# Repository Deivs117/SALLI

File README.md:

# SALLI: Salamander Autonomous Locomotion on Land Infrastructure

SALLI is an open-source, low-cost, and modular mechatronic platform designed to study bio-inspired terrestrial locomotion. Drawing inspiration from the sprawling gait of the salamander, this project integrates custom 3D-printed mechanical linkages, dedicated modular printed circuit boards (PCBs), lightweight embedded ESP-IDF firmware, and high-level Python control algorithms.

---

## Project Vision & Philosophy

Traditional robotics platforms often suffer from high manufacturing costs, complex monolithic assemblies, and poor reparability. SALLI was conceived under a different paradigm:
* **True Modularity:** Every physical segment—whether a spinal oscillator, a locomotor leg, or a sensory head—uses a standardized mechanical and electrical connection interface. Segments can be chain-linked dynamically to increase or decrease the robot's degrees of freedom (DoF).
* **Low Cost & Accessibility:** Designed to be accessible to students, researchers, and hobbyists. The structural parts are optimized for standard FDM 3D printing, and the electronics rely on budget-friendly, high-performance ESP32-C3 microcontrollers and standard micro servos.
* **Easy Maintenance & Repair:** Field repairs can be executed swiftly. Damage to a single segment does not compromise the whole robot; the offending module can be disconnected and swapped out in minutes.

---

## System Architecture

The project is structurally divided into four cohesive domains:

```mermaid
graph TD
    A[Control Codes - Python PC] <-->|UDP over Wi-Fi| B[Firmware - ESP-IDF Master AP]
    B <-->|UDP Multicast / Serial Bus| C[Firmware - ESP-IDF Slave Node]
    B -->|PWM Signals| D[Custom PCBs / Power Rails]
    C -->|PWM Signals| D
    D -->|Actuation| E[CAD 3D - Physical Modules]

```

1. **`CAD_3D/` (Mechanical Architecture):** Multi-segment structure utilizing bio-mimetic joint limits and sprawling kinematics.
2. **`PCBs/` (Electrical Architecture):** Modular bus system delivering isolated power lines (to prevent servo-induced voltage brownouts) and standardized signal traces.
3. **`Firmware/` (Embedded Systems):** High-efficiency ESP-IDF C-code implementing an Access Point control loop and UDP-based communication over ESP32-C3 chips.
4. **`ControlCodes/` (High-Level Control & Autonomy):** Python orchestrator supporting manual teleoperation, automatic parameter identification, and servo calibration.

---

## Repository Directory Tree

```text
SALLI/
├── .gitignore                   # Global file and directory exclusions
├── README.md                    # Root-level project documentation (This file)
│
├── CAD_3D/                      # Mechanical assemblies and components
│   ├── Cabeza V3/               # Sensory head module
│   ├── Cola/                    # Stabilizing tail segment
│   ├── Ensamble Total/          # Master digital design assembly
│   ├── Módulo de Patas V3/      # Sprawling leg kinematics module
│   ├── Oscilatorio V4/          # Daisy-chainable spinal segments
│   └── Patines/                 # Passive ground contact slide-pads
│
├── ControlCodes/                # High-level Python control ecosystem
│   ├── Calibration.py           # Multi-servo offset calibration utility
│   ├── SALLI.py                 # Core autonomy and CPG state engine
│   └── Teleoperation.py         # Human-in-the-loop manual controller
│
├── Firmware/                    # Low-level ESP-IDF software
│   ├── Acces Point Sally/       # Master AP, computational control, and state processor
│   └── WIFI_Movement/           # Slave node receiver executing raw joint positions
│
└── PCBs/                        # Electrical schematic and board layouts
    ├── Camera/                  # Visual feedback capture module
    ├── HeadModule/              # Central micro-controller carrier PCB
    ├── Legs_Module/             # High-current servo driver PCB
    └── Oscilatory/              # Passive signal-passthrough spine PCB

```

---

## Biological Locomotion Model

SALLI's movement is mathematically governed by a **Central Pattern Generator (CPG)** model. This system represents networks of coupled neural oscillators that generate rhythmic patterns without sensory feedback.

The phase relation between the body segments ($i$) and limbs ($j$) is modeled using coupled differential equations:

$$\frac{d\theta_i}{dt} = 2\pi \nu_i + \sum_{j} w_{ij} \sin(\theta_j - \theta_i - \phi_{ij})$$

Where:

* $\theta_i$ represents the instantaneous phase of the $i$-th oscillator.
* $\nu_i$ is the intrinsic frequency of the segment.
* $w_{ij}$ dictates the coupling strength between neighboring segments.
* $\phi_{ij}$ is the target phase bias defining traveling waves for swimming or crawling.

This math is processed in real-time between the `ControlCodes` layer and the `Firmware` layer to ensure fluid, life-like movements.

---

## Quick Start

### 1. Requirements & Tools

* **CAD:** Autodesk Fusion 360, SolidWorks, or FreeCAD to view STEP/STL files.
* **Firmware development:** Espressif ESP-IDF SDK (v5.1 or later recommended).
* **Control Station:** Python 3.10+ with standard networking libraries.

### 2. Basic Setup

To clone the repository and initialize the project:

```bash
git clone [https://github.com/YourUsername/SALLI.git](https://github.com/YourUsername/SALLI.git)
cd SALLI

```

---

## Academic Context

This project was developed at **Universidad Autónoma de Occidente (UAO)**, Cali, Colombia, within the Faculty of Engineering. It serves as an open-source platform to advance research in bio-inspired robotics, kinetic efficiency, and distributed embedded networks.

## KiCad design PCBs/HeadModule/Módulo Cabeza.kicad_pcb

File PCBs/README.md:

# SALLI: Custom Electronic PCBs

This directory contains the electrical designs for SALLI's custom printed circuit boards. The electronic system is engineered to solve a common pitfall in amateur robotics: messy, unreliable wiring harnesses that introduce high resistance, noise, and power failures.

---

## Electrical Architecture Overview

SALLI uses a decentralized, modular electrical bus system. Power is distributed along the spine via a ruggedized internal backbone, preventing major voltage drops from affecting the master microcontroller.

```mermaid
flowchart TD
    %% Definición de Bloques Principales
    Battery["Main Battery Pack<br>(2S LiPo / 7.4V)"]
    RegServo["Servo Regulators<br>(5V - 6V)"]
    RegLogic["Logic Regulators<br>(3.3V)"]
    
    %% Representación del Bus Centralizado
    subgraph Bus ["SALLI Power & Communication Bus"]
        direction LR
        Lines["Power Rails & Signal Traces"]
    end

    %% Módulos de Destino (PCBs)
    Head["HeadModule<br>(Master Processing)"]
    Osc["Oscilatory<br>(Spine Segment)"]
    Legs["Legs_Module<br>(High-Current Driver)"]

    %% Conexiones e Interconexión Eléctrica
    Battery ==>|Raw VCC| RegServo
    Battery -->|Raw VCC| RegLogic
    
    RegServo ==>|High-Current Servo VCC| Lines
    RegLogic -->|Isolated Clean 3.3V| Lines

    Lines ==> Head
    Lines ==> Osc
    Lines ==> Legs

    %% Estilos de Ingeniería Avanzada (Sin Emojis)
    style Battery fill:#1a1a1a,stroke:#bf616a,stroke-width:2px,color:#fff
    style RegServo fill:#2d2d2d,stroke:#d08770,stroke-width:1px,color:#fff
    style RegLogic fill:#2d2d2d,stroke:#ebcb8b,stroke-width:1px,color:#fff
    style Bus fill:#232831,stroke:#81a1c1,stroke-width:2px,color:#fff
    style Lines fill:#3b4252,stroke:#88c0d0,stroke-width:1px,color:#fff
    style Head fill:#1a1a1a,stroke:#4c566a,stroke-width:1px,color:#fff
    style Osc fill:#1a1a1a,stroke:#4c566a,stroke-width:1px,color:#fff
    style Legs fill:#1a1a1a,stroke:#4c566a,stroke-width:1px,color:#fff
    
    %% Definición de grosores de línea para diferenciar potencia de lógica
    linkStyle 0 stroke:#bf616a,stroke-width:3px;
    linkStyle 1 stroke:#ebcb8b,stroke-width:1px;
    linkStyle 2 stroke:#d08770,stroke-width:3px;
    linkStyle 3 stroke:#ebcb8b,stroke-width:1px;
```

---

## Board Subsystems & Responsibilities

The electrical system is divided into four main board profiles:

### 1. `HeadModule` (Master Processing PCB)

The central board of the robot, acting as SALLI's head controller.

* **MCU Support:** Integrates the footprint for the **ESP32-C3 Mini** board.
* **Power Filtering:** Features heavy ceramic and electrolytic capacitor banks to filter out high-frequency noise induced by servo inductive kickbacks.
* **Sensor Hub:** Routes dedicated pins for IMUs (Inertial Measurement Units for tilt and balance detection) and external range sensors.

### 2. `Oscilatory` (Spine Segment PCB)

These are passive/semi-active distribution boards designed to be chain-linked together.

* **The SALLI Bus:** Passes power (VCC and GND) and communication channels downstream to consecutive modules.
* **Servo Tap:** Provides local, filtered power connectors for the local spinal deflection servo, keeping cabling lengths under $20\text{ mm}$.

### 3. `Legs_Module` (High-Current Driver Board)

Because the limbs support the entire weight of the robot and drive forward crawling forces, they demand significant active currents.

* **High-Current Traces:** Features wide copper traces capable of handling sustained currents of up to $3\text{ A}$ during crawling cycles.
* **Independent Power Regulation:** Standardizes opto-couplers or isolation resistors to prevent sudden physical motor stalls from corrupting the main microcontroller's logical operations.

### 4. `Camera` (Vision Expansion Board)

An optional expansion PCB tailored to hold camera modules (such as ESP32-CAM or specialized small SPI cameras) to enable visual-spatial telemetry.

---

## Design Guidelines

* **Trace Width Selection:** * Power paths ($VCC\_SERVO$, $GND$) are set to a minimum of `1.5 mm` width to minimize resistance and prevent thermal stress under heavy load.
* Logic lines ($TX$, $RX$, $PWM$) are kept at standard `0.254 mm` traces.

* **Decoupling Strategy:** Each module places a `100uF` electrolytic capacitor directly in parallel with the local servo power terminal, supplemented by a standard `0.1uF` ceramic capacitor close to the logic rails to handle high-frequency voltage ripples.
* **Standardized Pin Headers:** Connectors use standard, highly accessible, polarized headers (like JST-XH or XT30/XT60 for power entry) to ensure mistake-proof assembly by students.

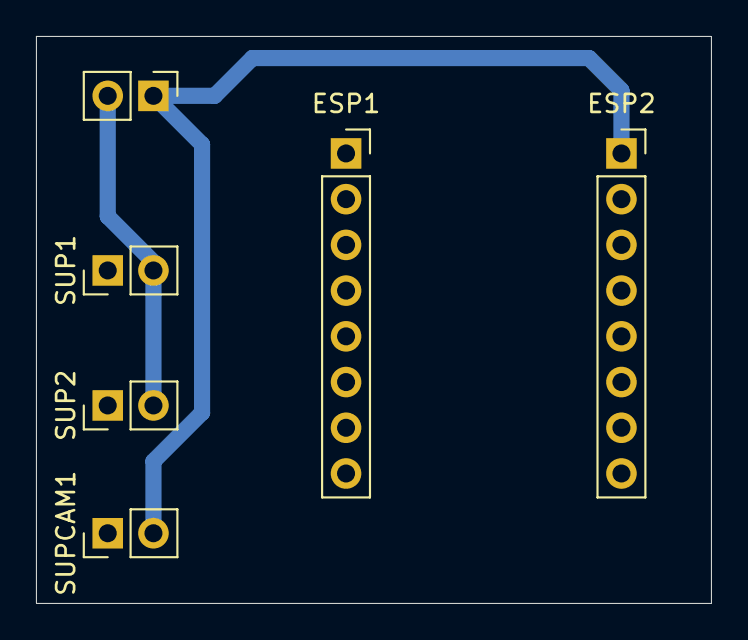
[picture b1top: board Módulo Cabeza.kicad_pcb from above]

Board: 2 copper layers, 37.5 x 31.5 mm, 6 parts (0 on the bottom side), 3 nets.

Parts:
ESP1, ESP2: Conn_01x08; PinSocket_1x08_P2.54mm_Vertical
SUP1, SUP2: Supply; PinHeader_1x02_P2.54mm_Vertical
SUPCAM1: Supply; PinHeader_1x02_P2.54mm_Vertical
SWITCH1: Supply; PinHeader_1x02_P2.54mm_Vertical

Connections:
GND: ESP2.2, SUP1.1, SUP2.1, SUPCAM1.1
V+: ESP2.1, SUPCAM1.2, SWITCH1.1
VCC: SUP1.2, SUP2.2, SWITCH1.2

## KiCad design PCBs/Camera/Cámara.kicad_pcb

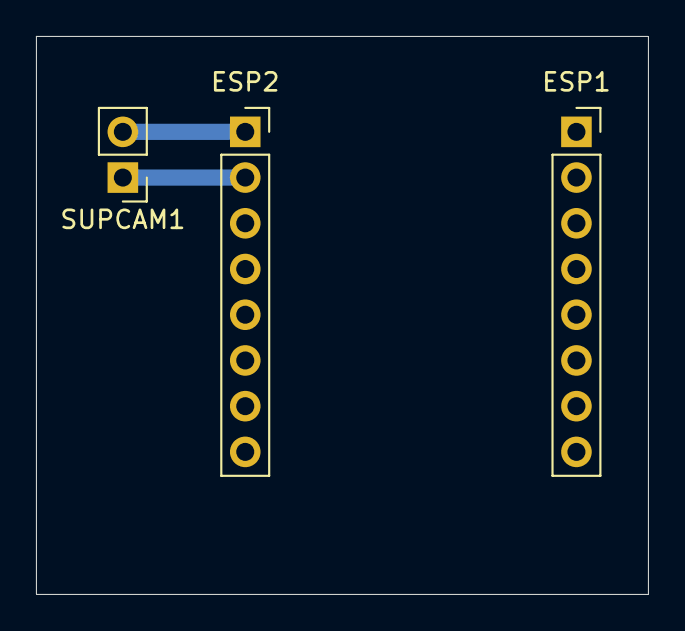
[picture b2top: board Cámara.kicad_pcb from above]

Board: 2 copper layers, 34.0 x 31.0 mm, 3 parts (0 on the bottom side), 2 nets.

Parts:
ESP1, ESP2: Conn_01x08; PinSocket_1x08_P2.54mm_Vertical
SUPCAM1: Supply; PinHeader_1x02_P2.54mm_Vertical

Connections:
GND: ESP2.2, SUPCAM1.1
V+: ESP2.1, SUPCAM1.2

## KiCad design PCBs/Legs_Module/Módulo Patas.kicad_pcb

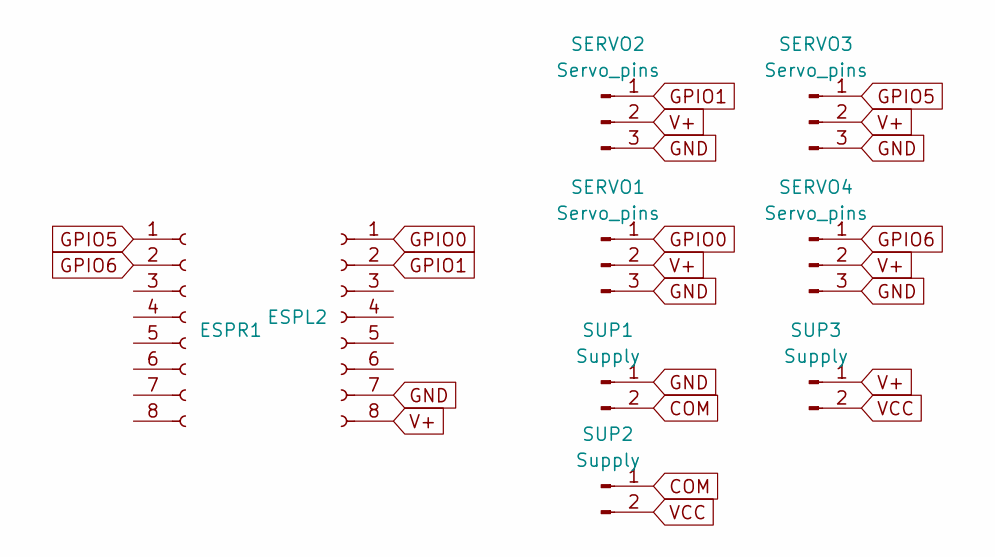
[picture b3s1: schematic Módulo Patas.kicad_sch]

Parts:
ESPL2: Conn_01x08_Socket; PinSocket_1x08_P2.54mm_Vertical
ESPR1: Conn_01x08_Socket; PinSocket_1x08_P2.54mm_Vertical
SERVO1, SERVO2, SERVO3, SERVO4: Servo_pins; PinHeader_1x03_P2.54mm_Vertical
SUP1, SUP2, SUP3: Supply; PinHeader_1x02_P2.54mm_Vertical

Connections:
COM: SUP1.2, SUP2.1
GND: ESPL2.7, SERVO1.3, SERVO2.3, SERVO3.3, SERVO4.3, SUP1.1
GPIO0: ESPL2.1, SERVO1.1
GPIO1: ESPL2.2, SERVO2.1
GPIO5: ESPR1.1, SERVO3.1
GPIO6: ESPR1.2, SERVO4.1
V+: ESPL2.8, SERVO1.2, SERVO2.2, SERVO3.2, SERVO4.2, SUP3.1
VCC: SUP2.2, SUP3.2

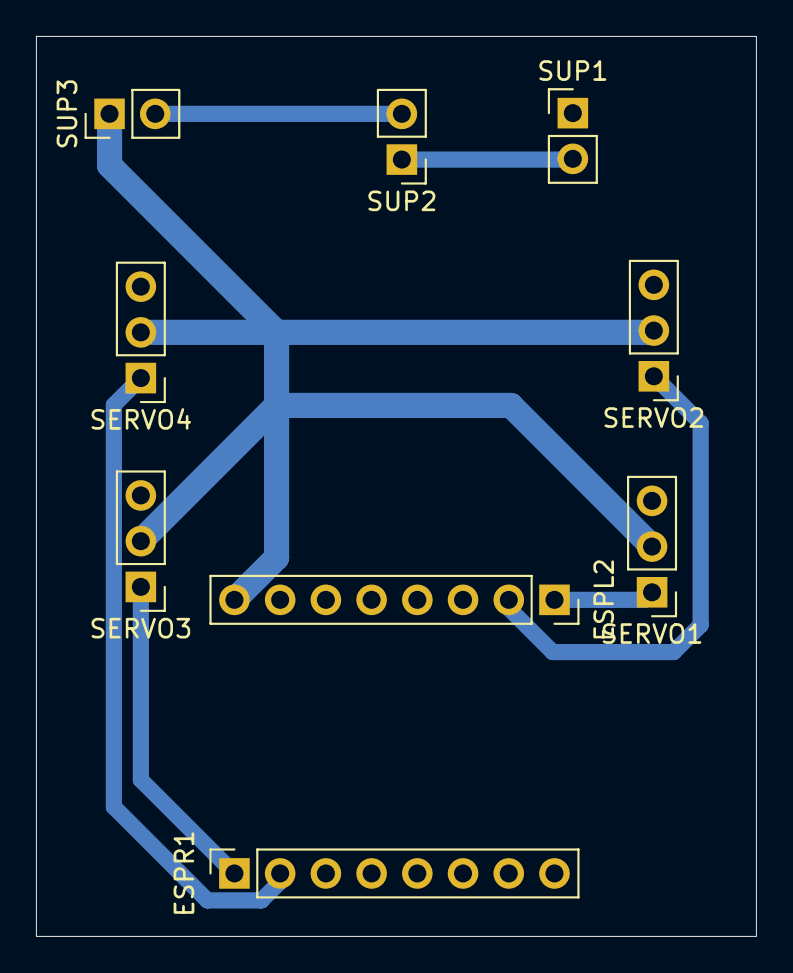
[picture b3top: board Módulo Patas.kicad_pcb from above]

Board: 2 copper layers, 40.0 x 50.0 mm, 9 parts (0 on the bottom side), 8 nets.

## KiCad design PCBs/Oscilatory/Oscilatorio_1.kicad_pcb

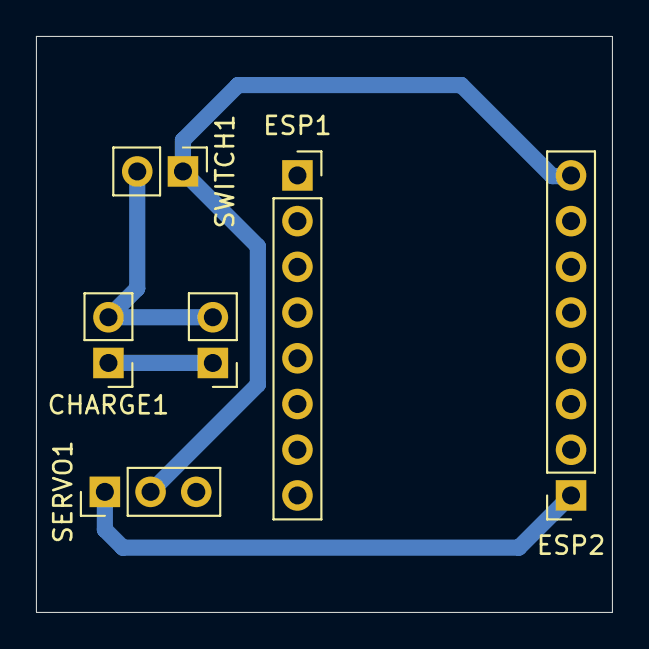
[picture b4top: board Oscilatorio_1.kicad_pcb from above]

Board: 2 copper layers, 32.0 x 32.0 mm, 6 parts (0 on the bottom side), 4 nets.

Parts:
CHARGE1: Supply; PinHeader_1x02_P2.54mm_Vertical
ESP1, ESP2: Conn_01x08_Socket; PinSocket_1x08_P2.54mm_Vertical
SERVO1: Servo_pins; PinHeader_1x03_P2.54mm_Vertical
SUP1: Supply; PinHeader_1x02_P2.54mm_Vertical
SWITCH1: Supply; PinHeader_1x02_P2.54mm_Vertical

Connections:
GND: CHARGE1.1, ESP2.7, SERVO1.3, SUP1.1
GPIO0: ESP2.1, SERVO1.1
V+: ESP2.8, SERVO1.2, SWITCH1.1
VCC: CHARGE1.2, SUP1.2, SWITCH1.2

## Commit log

2026-06-19 Removed README.md from Firmware/WIFI_Movement
2026-06-19 Add README.md
2026-06-19 Add README files
2026-06-21 update documentation
2026-06-28 update git ignore
2026-06-28 update ncs deletions
2026-06-28 update backups deletions
